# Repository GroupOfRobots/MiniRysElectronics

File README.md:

# RyśBoard Hardware Controller

This project involves the design and development of the RyśBoard hardware controller, a custom PCB created to manage a robotic system. The project aims to enhance the performance of the previous controller and involves various stages such as component selection, PCB manufacturing, and assembly. The documentation outlines the key sections of the controller, its power sources, communication interfaces, and overall production process.

## Table of Contents

1. [Key Sections of the Controller](#key-sections-of-the-controller)
   - [24V Power Supply](#24v-power-supply)
   - [5V Power Supply](#5v-power-supply)
   - [Motor Drivers](#motor-drivers)
   - [Battery Voltage Monitoring](#battery-voltage-monitoring)
   - [Battery Connectors](#battery-connectors)
   - [I/O Connectors](#io-connectors)
   - [Configurable Indicators](#configurable-indicators)
   - [Mounting Options](#mounting-options)
3. [Production Process](#production-process)
   - [Initial Project Design](#initial-project-design)
   - [Final Design in KiCad](#final-design-in-kicad)
   - [PCB Assembly](#pcb-assembly)

---

## Project Overview

This report summarizes the development of the RyśBoard hardware controller, which underwent several updates to improve its functionality. The work involved ordering components, manufacturing and assembling the PCBs, and evaluating the performance of the power supply systems.

---

## Key Sections of the Controller

### 24V Power Supply

The 24V power supply is based on the LM51231-Q1 chip and provides up to 2.5A, delivering max 60W of power. This ensures sufficient power for the stepper motors and their drivers, with a margin to accommodate future increases in power requirements.

### 5V Power Supply

A TPS565242-based 5V power supply provides up to 4A, delivering max 20W of power. It is designed to power the Raspberry Pi 4 and Raspberry Pi 5, allowing for smooth operation even with additional accessories such as fans.

### Motor Drivers

The motor drivers use L6470H chips, which meet the requirements of the stepper motors (drawing up to 1A per driver under full load). These drivers are essential for stabilizing motor control.

### Battery Voltage Monitoring

The MAX11613 ADC monitors the voltage of three batteries, each connected to a separate channel. This information is communicated to the control unit via an I²C bus, allowing real-time monitoring of battery status.

### Battery Connectors

Three battery connectors are currently used, but due to their large size, there may be a future revision to consolidate them into a single, more compact connector to optimize space on the PCB.

### I/O Connectors

The board includes dedicated connectors for each stepper motor, eight connectors for I²C sensors, and one connector each for SPI and UART devices. A 5V fan connector is also available for cooling.

### Configurable Indicators

The board is equipped with configurable LEDs (red and green) connected to GPIO pins 23 and 24 on the control unit. These can be used to signal different status conditions.

### Mounting Options

The controller is compatible with the Raspberry Pi HAT standard, allowing easy integration with Raspberry Pi systems. Care has been taken to ensure electrical insulation and secure mounting.

---

## Production Process

### Initial Project Design

The initial design phase involved five key tasks:
1. Designing the HAT-compliant add-on board for Raspberry Pi.
2. Proper placement of components for the 24V and 5V power supplies.
3. Ensuring effective heat dissipation for the motor drivers.
4. Positioning passive components for ADC and other peripherals.
5. Routing power and signal paths.

### Final Design in KiCad

The KiCad design process was iterative, focusing on:
- Component placement to ensure efficient routing.
- Optimizing power trace lengths and widths for lower heat generation and energy loss.
- Optimizing signal trace lengths and placement for lower crosstalk.
- Revising the transistor selection for the 24V power supply to improve efficiency and component availability.

Final modifications included changing the location of key components for better thermal management and adding identification markings for easier assembly.

### PCB Assembly

The assembly phase involved:
1. Ordering components primarily from Mouser Electronics.
2. Soldering the components onto the PCB.
3. Inspecting the board for any mechanical defects, such as excess solder or improper connections.

The PCB assembly required soldering both the top and bottom components, with careful attention to ensure proper connections and functionality.

---

## Project Status

- **Current version**: Final (PCB ver. 1.1)
- **Changes since last iteration**: Fixed problems with stability of internal voltage regulators of L6470H drivers

---

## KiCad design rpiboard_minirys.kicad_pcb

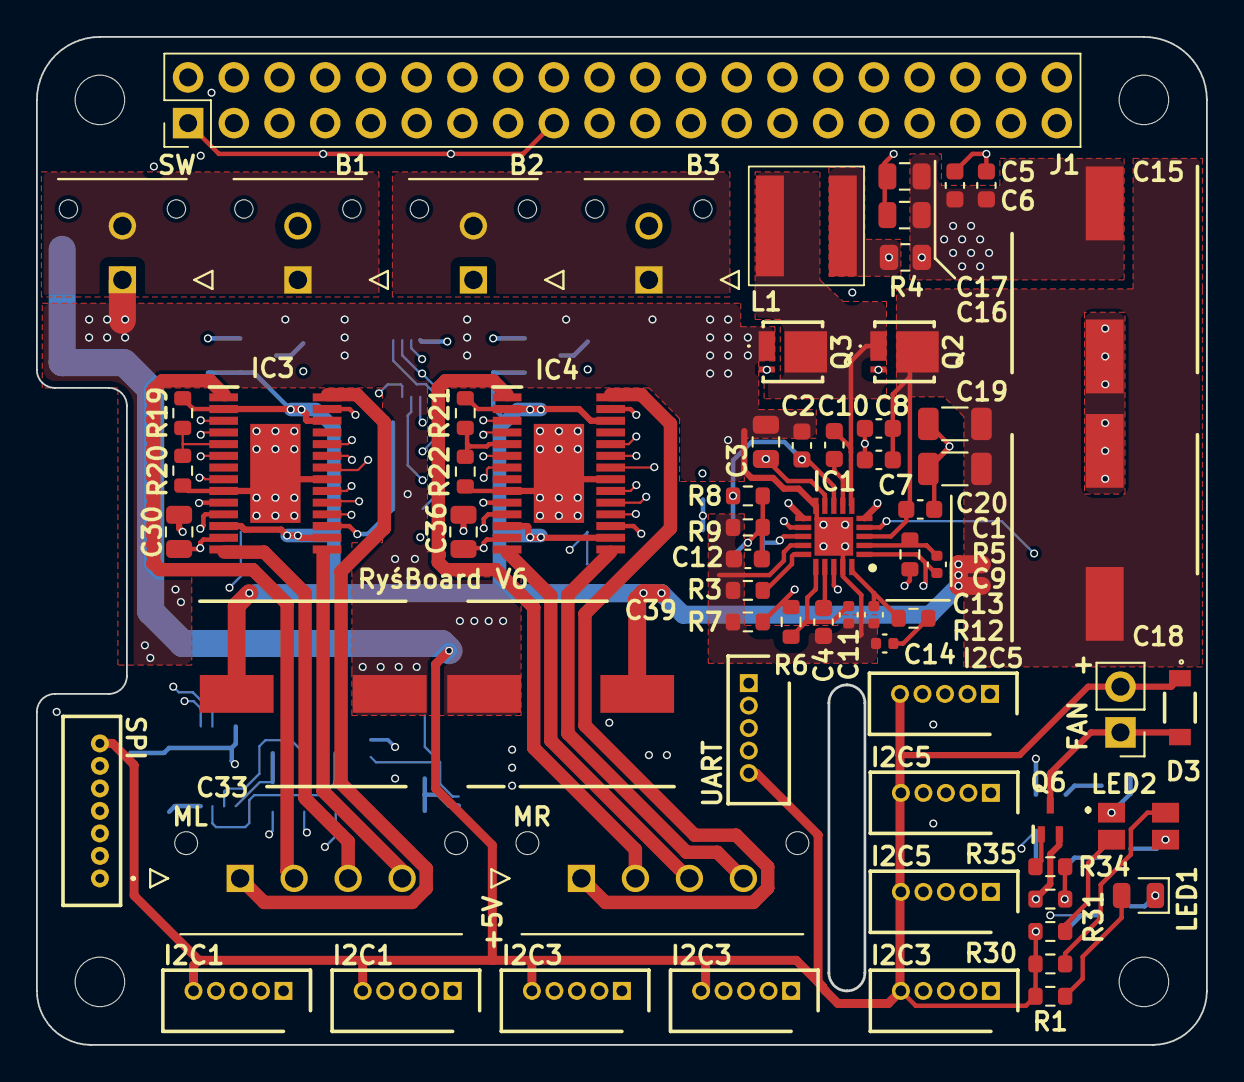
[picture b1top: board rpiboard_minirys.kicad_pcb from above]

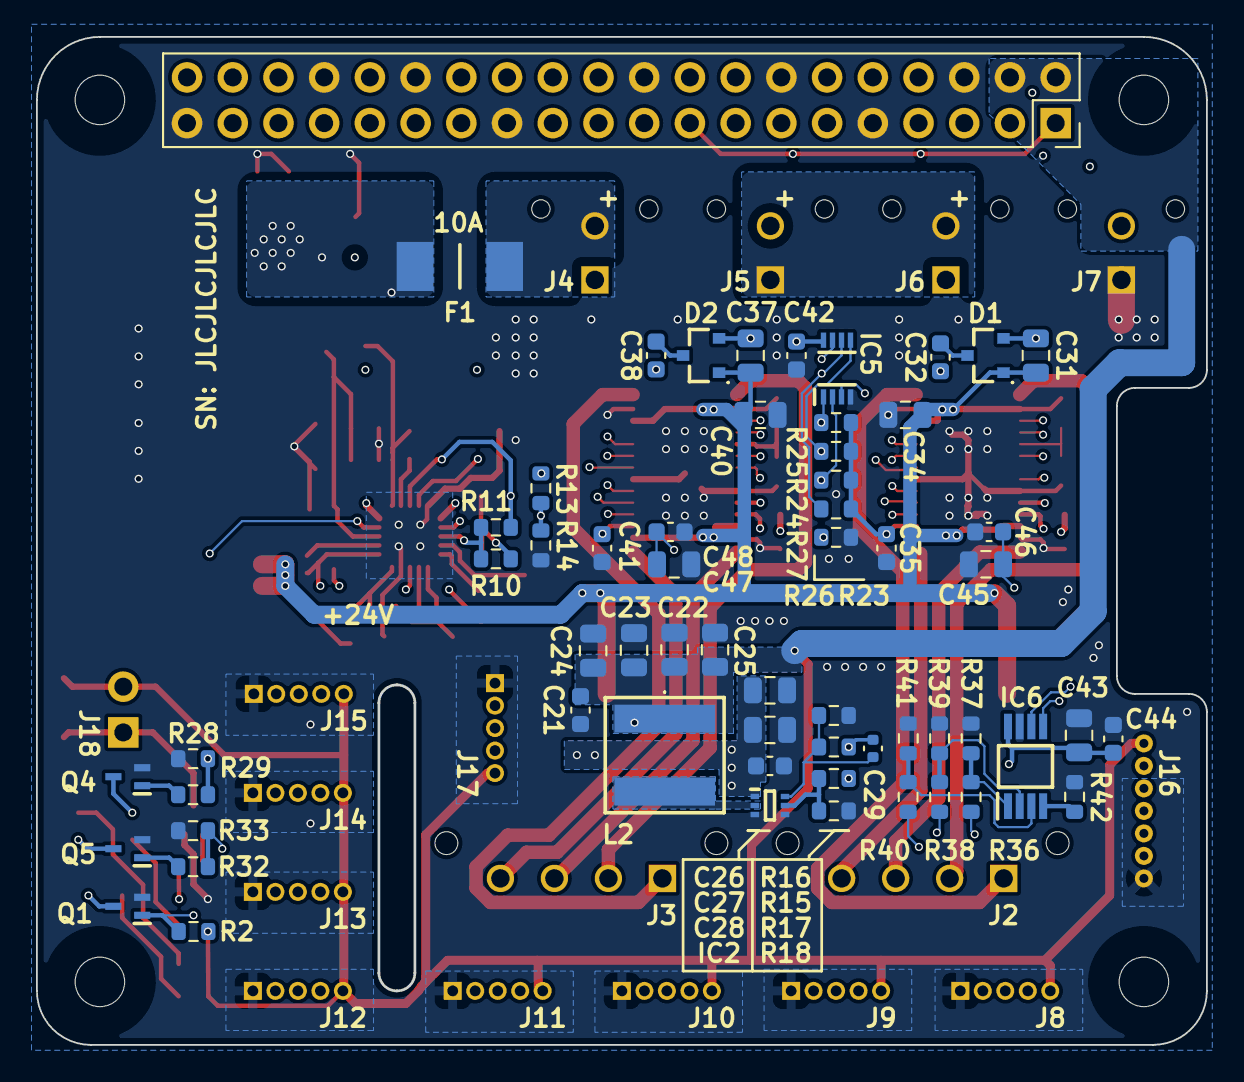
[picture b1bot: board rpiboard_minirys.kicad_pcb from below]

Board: 4 copper layers, 65.0 x 56.0 mm, 132 parts (60 on the bottom side), 93 nets.

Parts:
C1, C2, C5, C6, C7, C8, C10, C21, C28, C35, C41, C42, C44, C46, C48: 100nF; C_0603_1608Metric
C3, C43: 4.7uF; C_0805_2012Metric
C4, C12: 330nF; C_0603_1608Metric
C9: 100pF; C_0402_1005Metric
C11: 470pF; C_0402_1005Metric
C13: 22pF; C_0402_1005Metric
C14: 1.5nF; C_0402_1005Metric
C15, C18, C33, C39: 100uF; CAPAE1030X1100N
C16, C17, C22, C23, C24, C25, C26, C27, C30, C36, C45, C47: 10uF; C_0805_2012Metric
C19, C20: 10uF/50V; C_1206_3216Metric
C29: 33pF; C_0402_1005Metric
C31, C34, C37, C40: 220nF; C_0805_2012Metric
C32, C38: 10nF; C_0603_1608Metric
D1, D2: BAV99; BAV99215
D3: BAT54GWX; SOD123
F1: 10A Fuse; FUSC6126X270N
H1, H2, H3, H4: MountingHole; RPi_Hat_Mounting_Hole
IC1: LM51231QRGRRQ1; QFN50P350X350X100-21N-D
IC2: TPS564242DRLR; SOTFL50P160X60-6N
IC3, IC4: L6470H; SOP65P640X120-29N
IC5: 74AUP2G00DC,125; SOP50P310X100-8N
IC6: MAX11613EUA+T; SOP65P490X110-8N
J1: RPi_GPIO; PinSocket_2x20_P2.54mm_Vertical
J2: Motor_L; 43650-04YY_151617
J3: Motor_R; 43650-04YY_151617
J4: B_Cell_3; 43045-02YY_121314
J5: B_Cell_2; 43045-02YY_121314
J6: B_Cell_1; 43045-02YY_121314
J7: SW; 43045-02YY_121314
J8: Temp_Sensor; 530470510
J9: IMU_Sensor; 530470510
J10: ToF1_Sensor; 530470510
J11: ToF2_Sensor; 530470510
J12: ToF3_Sensor; 530470510
J13: ToF4_Sensor; 530470510
J14: ToF5_Sensor; 530470510
J15: ToF6_Sensor; 530470510
J16: SPI_Connector; 530470710
J17: UART_Connector; 530470510
J18: Fan_Connector; PinHeader_1x02_P2.54mm_Vertical
L1: SRP6060FA-4R7M; SRP6060FA4R7M
L2: SRP6050CA-1R8M; SRP6050CA1R8M
LED1: GREEN; LED_0805_2012Metric
LED2: LSG_T676-P7Q7-1+N7P7-24; LSGT676P7Q71N7P724
Q1, Q4, Q5, Q6: DMG1012T-7; SOT50P160X80-3N
Q2, Q3: ISZ065N03L5S; ISZ065N03L5SATMA1
R1, R29, R30, R31, R32, R35: 150R; R_0603_1608Metric
R2, R9: 12k; R_0603_1608Metric
R3: 32.4k/.1%; R_0603_1608Metric
R4: 0.006R; R_0805_2012Metric
R5: 100R; R_0603_1608Metric
R6: 21k; R_0603_1608Metric
R7: 14k; R_0603_1608Metric
R8: 80.6k; R_0603_1608Metric
R10, R11, R13, R14: 0R; R_0603_1608Metric
R12: 59k; R_0603_1608Metric
R15: 220k; R_0603_1608Metric
R16: 30k; R_0603_1608Metric
R17, R28, R33, R34: 100k; R_0603_1608Metric
R18: 17.4k; R_0603_1608Metric
R19, R21: 27k; R_0603_1608Metric
R20, R22, R37, R39, R41, R42: 10k; R_0603_1608Metric
R23, R24, R25, R26, R27: 38.3k; R_0603_1608Metric
R36: 15k; R_0603_1608Metric
R38: 36k; R_0603_1608Metric
R40: 56k; R_0603_1608Metric

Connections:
+3.3V: C30.1, C35.2, C36.1, C41.2, C42.1, C43.1, C44.1, IC3.4 (SW), IC3.17 (VDD), IC4.4 (SW), IC4.17 (VDD), IC5.8 (VCC), IC6.8 (VDD), J1.1, J1.17, R24.1, R25.1, R26.1, R27.1
+5V: C21.1, C22.1, C23.1, C24.1, C25.1, C29.2, D3.1 (K), J1.2, J1.4, J8.5, J9.5, J10.5, J11.5, J12.5, J13.5, J14.5, J15.5, J16.7, J17.5, J18.2, L2.1, R1.1, R2.2, R15.1, R30.2, R31.2
+24V: C1.2, C7.1, C8.1, C18.1, C19.1, C20.1, C31.2, C33.1, C34.2, C37.2, C39.1, C40.2, D1.1 (A), D2.1 (A), IC1.3 (VOUT/SENSE), IC3.2 (VSA_1), IC3.12 (VSB_1), IC3.16 (VSB_2), IC3.26 (VSA_2), IC4.2 (VSA_1), IC4.12 (VSB_1), IC4.16 (VSB_2), IC4.26 (VSA_2), Q2.3 (D), R19.2, R21.2
/Connectors/CELL_1: J5.1, J6.2, R36.1
/Connectors/CELL_2: J4.1, J5.2, R38.1
/Connectors/CELL_3: F1.2, J4.2, R40.1
/Connectors/FAN_PWM: J1.12, R34.1, R35.1
/Connectors/FAN_SW: D3.2 (A), J18.1, Q6.3 (D)
/Connectors/I2C1_SCL: IC6.5 (SCL), J1.5, J8.3, J9.3
/Connectors/I2C1_SDA: IC6.6 (SDA), J1.3, J8.4, J9.4
/Connectors/I2C3_SCL: J1.29, J10.3, J11.3, J12.3
/Connectors/I2C3_SDA: J1.7, J10.4, J11.4, J12.4
/Connectors/I2C5_SCL: J1.33, J13.3, J14.3, J15.3
/Connectors/I2C5_SDA: J1.32, J13.4, J14.4, J15.4
/Connectors/LED_GREEN: J1.18, R32.2, R33.1
/Connectors/LED_RED: J1.16, R28.2, R29.1
/Connectors/ML_OUT1A: IC3.1 (OUT1A), J2.2
/Connectors/ML_OUT1B: IC3.14 (OUT1B), J2.3
/Connectors/ML_OUT2A: IC3.28 (OUT2A), J2.1
/Connectors/ML_OUT2B: IC3.15 (OUT2B), J2.4
/Connectors/MR_OUT1A: IC4.1 (OUT1A), J3.2
/Connectors/MR_OUT1B: IC4.14 (OUT1B), J3.3
/Connectors/MR_OUT2A: IC4.28 (OUT2A), J3.1
/Connectors/MR_OUT2B: IC4.15 (OUT2B), J3.4
/Connectors/M_BUSY: IC5.3 (2Y), J1.13
/Connectors/M_FLAG: IC5.7 (1Y), J1.11
/Connectors/SPI_CLK: IC3.19 (CK), IC4.19 (CK), J1.23, J16.4
/Connectors/SPI_IRQ: J1.22, J16.2
/Connectors/SPI_MISO: IC4.18 (SDO), J1.21, J16.5
/Connectors/SPI_MOSI: IC3.20 (SDI), J1.19, J16.6
/Connectors/TOF1_EN: J1.31, J10.2
/Connectors/TOF2_EN: J1.36, J11.2
/Connectors/TOF3_EN: J1.35, J12.2
/Connectors/TOF4_EN: J1.38, J13.2
/Connectors/TOF5_EN: J1.40, J14.2
/Connectors/TOF6_EN: J1.37, J15.2
/Connectors/UART_RX: J1.10, J17.4
/Connectors/UART_TX: J1.8, J17.3
/Connectors/~M_STBY: IC3.3 (~STBY/RST), IC4.3 (~STBY/RST), J1.15, R23.2
/Connectors/~SPI_CS_E: J1.26, J16.3
/Connectors/~SPI_CS_M: IC3.23 (~CS), IC4.23 (~CS), J1.24
/Motor_Controllers/3V_VREG_ML: C45.1, C46.1, IC3.6 (VREG)
/Motor_Controllers/3V_VREG_MR: C47.1, C48.1, IC4.6 (VREG)
/Motor_Controllers/CLK_SYNC: IC3.8 (OSCOUT), IC4.7 (OSCIN)
/Motor_Controllers/ML_ADCIN: IC3.5 (ADCIN), R19.1, R20.2
/Motor_Controllers/ML_CP: C32.2, IC3.10 (CP)
/Motor_Controllers/ML_VBOOT: C31.1, D1.2 (K), IC3.11 (VBOOT)
/Motor_Controllers/MR_ADCIN: IC4.5 (ADCIN), R21.1, R22.2
/Motor_Controllers/MR_CP: C38.2, IC4.10 (CP)
/Motor_Controllers/MR_VBOOT: C37.1, D2.2 (K), IC4.11 (VBOOT)
/Motor_Controllers/SPI_BRIDGE: IC3.18 (SDO), IC4.20 (SDI)
/Motor_Controllers/~ML_BUSY: IC3.22 (~BUSY/SYNC), IC5.5 (2A), R24.2
/Motor_Controllers/~ML_FLAG: IC3.24 (~FLAG), IC5.1 (1A), R25.2
/Motor_Controllers/~MR_BUSY: IC4.22 (~BUSY/SYNC), IC5.6 (2B), R26.2
/Motor_Controllers/~MR_FLAG: IC4.24 (~FLAG), IC5.2 (1B), R27.2
/Supply_24V/COMP: C13.1, IC1.20 (COMP), R12.1
/Supply_24V/CSN: C9.1, IC1.2 (CSN), R5.1
/Supply_24V/HB: C10.1, IC1.7 (HB)
/Supply_24V/HO: IC1.5 (HO), Q2.2 (G)
/Supply_24V/LO: IC1.11 (LO), Q3.2 (G)
/Supply_24V/MODE: IC1.12 (MODE), R13.1, R14.1
/Supply_24V/SW: C10.2, IC1.6 (SW), L1.2, Q2.1 (S), Q3.3 (D)
/Supply_24V/TRK: IC1.18 (TRK), R6.2, R7.1
/Supply_24V/UVLO: IC1.13 (UVLO/EN), R10.1, R11.1
/Supply_24V/VCC_REG: C3.1, IC1.9 (VCC), R13.2
/Supply_24V/VREF: C11.1, IC1.16 (VREF/_RANGE), R6.1
GND: C1.1, C2.2, C3.2, C4.1, C5.2, C6.2, C7.2, C8.2, C11.2, C12.2, C13.2, C14.2, C15.2, C16.2, C17.2, C18.2, C19.2, C20.2, C21.2, C22.2, C23.2, C24.2, C25.2, C26.2, C27.2, C28.2, C30.2, C33.2, C34.1, C35.1, C36.2, C39.2, C40.1, C41.1, C42.2, C43.2, C44.2, C45.2, C46.2, C47.2, C48.2, IC1.10 (PGND), IC1.14 (SYNC/DITHER/VH), IC1.19 (AGND), IC1.21 (EP), IC2.3 (GND), IC2.4 (AGND), IC3.9 (AGND), IC3.13 (PGND_1), IC3.21 (DGND), IC3.27 (PGND_2), IC3.29 (EP), IC4.9 (AGND), IC4.13 (PGND_1), IC4.21 (DGND), IC4.27 (PGND_2), IC4.29 (EP), IC5.4 (GND), IC6.7 (GND), J1.6, J1.9, J1.14, J1.20, J1.25, J1.30, J1.34, J1.39, J7.1, J8.1, J9.1, J10.1, J11.1, J12.1, J13.1, J14.1, J15.1, J16.1, J17.1, Q1.2 (S), Q3.1 (S), Q4.2 (S), Q5.2 (S), Q6.2 (S), R3.2, R7.2, R9.2, R14.2, R16.2, R18.2, R20.1, R22.1, R23.1, R28.1, R33.2, R34.2, R37.2, R39.2, R41.2, R42.2
unnamed: C12.1, R8.2, R9.1, R10.2
unnamed: C14.1, R12.2
unnamed: C32.1, D1.3 (common)
unnamed: C38.1, D2.3 (common)
unnamed: IC1.4 (PGOOD), Q1.1 (G), R2.1
unnamed: IC1.15 (RT), R3.1
unnamed: C4.2, IC1.17 (SS)
unnamed: IC2.5 (EN), R17.2, R18.1
unnamed: C29.1, IC2.6 (FB), R15.2, R16.1
unnamed: IC2.2 (SW), L2.2
unnamed: IC6.1 (AIN0), R36.2, R37.1
unnamed: IC6.2 (AIN1), R38.2, R39.1
unnamed: IC6.3 (AIN2), R40.2, R41.1
unnamed: IC6.4 (AIN3/REF), R42.1
unnamed: J6.1, J7.2
unnamed: L1.1, R4.2, R5.2
unnamed: LED1.2 (A), R1.2
unnamed: LED1.1 (K), Q1.3 (D)
unnamed: LED2.1 (A1), Q4.3 (D)
unnamed: LED2.3 (A2), Q5.3 (D)
unnamed: LED2.2 (K1), R30.1
unnamed: LED2.4 (K2), R31.1
unnamed: Q4.1 (G), R29.2
unnamed: Q5.1 (G), R32.1
unnamed: Q6.1 (G), R35.2
VCC: C2.1, C5.1, C6.1, C9.2, C15.1, C16.1, C17.1, C26.1, C27.1, C28.1, F1.1, IC1.1 (CSP), IC1.8 (BIAS), IC2.1 (VIN), R4.1, R8.1, R11.2, R17.1

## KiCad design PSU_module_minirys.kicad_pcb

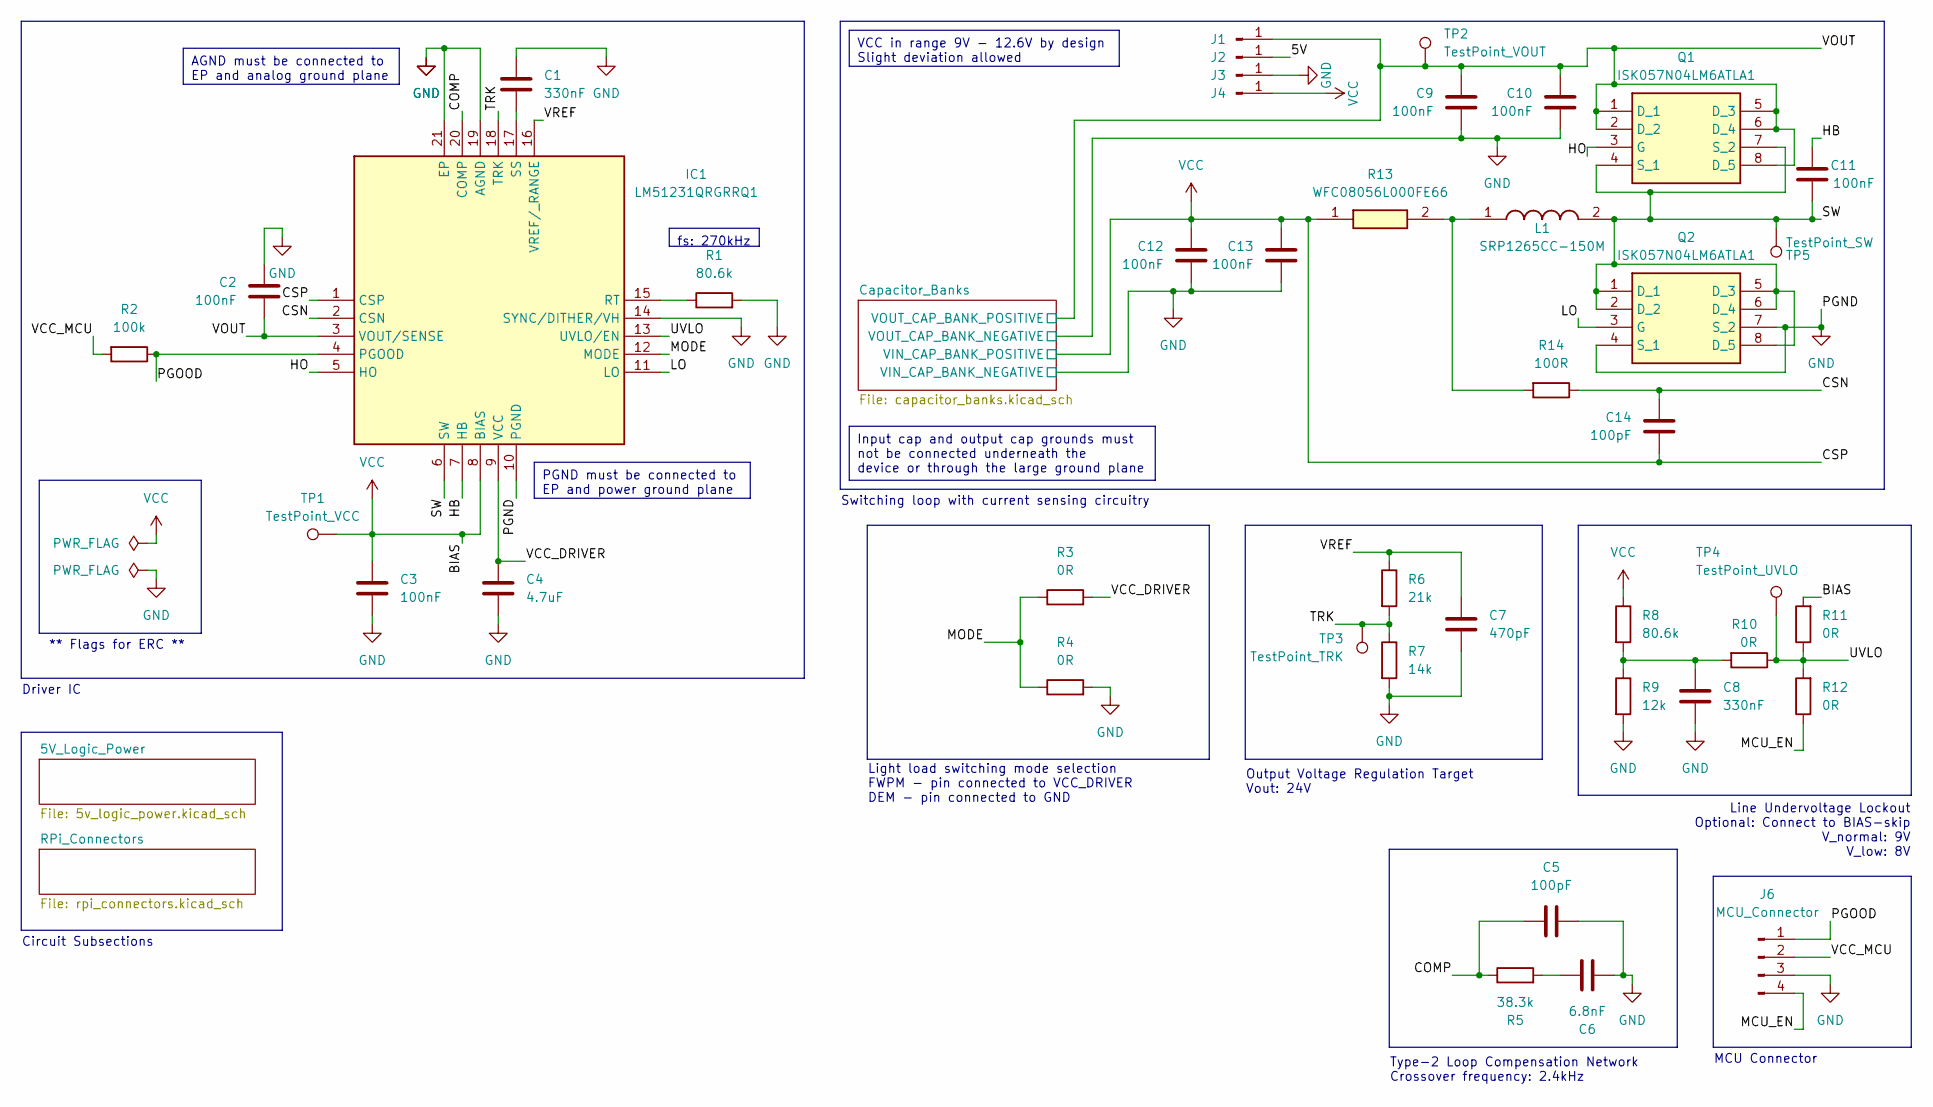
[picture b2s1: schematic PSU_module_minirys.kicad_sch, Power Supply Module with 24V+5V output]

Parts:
C1, C8: 330nF; C_0603_1608Metric
C2, C3, C9, C10, C11, C12, C13: 100nF; C_0603_1608Metric
C4: 4.7uF; C_0805_2012Metric
C5, C14: 100pF; C_0603_1608Metric
C6: 6.8nF; C_0603_1608Metric
C7: 470pF; C_0603_1608Metric
IC1: LM51231QRGRRQ1; QFN50P350X350X100-21N-D; Mouser Part Number 595-LM51231QRGRRQ1
J1, J2, J3, J4: Conn_01x01_Pin; TestPoint_Pad_2.0x2.0mm
J6: MCU_Connector; PinSocket_1x04_P2.54mm_Vertical
L1: SRP1265CC-150M; INDPM135125X650N; Manufacturer_Part_Number SRP1265CC-150M
Q1, Q2: ISK057N04LM6ATLA1; Manufacturer_Part_Number ISK057N04LM6ATLA1
R1, R8: 80.6k; R_0603_1608Metric
R2: 100k; R_0603_1608Metric
R3, R4, R10, R11, R12: 0R; R_0603_1608Metric
R5: 38.3k; R_0603_1608Metric
R6: 21k; R_0603_1608Metric
R7: 14k; R_0603_1608Metric
R9: 12k; R_0603_1608Metric
R13: WFC08056L000FE66; RESC2013X85N; Mouser Part Number 71-WFC08056L000FE66
R14: 100R; R_0603_1608Metric
TP1: TestPoint_VCC; TestPoint_Pad_D1.0mm
TP2: TestPoint_VOUT; TestPoint_Pad_D1.0mm
TP3: TestPoint_TRK; TestPoint_Pad_D1.0mm
TP4: TestPoint_UVLO; TestPoint_Pad_D1.0mm
TP5: TestPoint_SW; TestPoint_Pad_D1.0mm

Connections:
/5V: J2.1
/COMP: C5.1, IC1.20 (COMP), R5.1
/CSN: C14.1, IC1.2 (CSN), R14.1
/HB: C11.1, IC1.7 (HB)
/HO: IC1.5 (HO), Q1.3 (G)
/LO: IC1.11 (LO), Q2.3 (G)
/MCU_EN: J6.4, R12.1
/MODE: IC1.12 (MODE), R3.1, R4.1
/PGOOD: IC1.4 (PGOOD), J6.1, R2.1
/SW: C11.2, IC1.6 (SW), L1.2, Q1.4 (S_1), Q1.7 (S_2), Q2.1 (D_1), Q2.2 (D_2), Q2.5 (D_3), Q2.6 (D_4), Q2.8 (D_5), TP5.1
/TRK: IC1.18 (TRK), R6.2, R7.1, TP3.1
/UVLO: IC1.13 (UVLO/EN), R10.1, R11.1, R12.2, TP4.1
/VCC_DRIVER: C4.1, IC1.9 (VCC), R3.2
/VCC_MCU: J6.2, R2.2
/VOUT: C2.2, C9.1, C10.1, IC1.3 (VOUT/SENSE), J1.1, Q1.1 (D_1), Q1.2 (D_2), Q1.5 (D_3), Q1.6 (D_4), Q1.8 (D_5), TP2.1; also elsewhere on the board
/VREF: C7.1, IC1.16 (VREF/_RANGE), R6.1
GND: C1.1, C2.1, C3.2, C4.2, C5.2, C6.2, C7.2, C8.2, C9.2, C10.2, C12.2, C13.2, IC1.10 (PGND), IC1.14 (SYNC/DITHER/VH), IC1.19 (AGND), IC1.21 (EP), J3.1, J6.3, Q2.4 (S_1), Q2.7 (S_2), R1.2, R4.2, R7.2, R9.2; also elsewhere on the board
unnamed: C6.1, R5.2
unnamed: C8.1, R8.2, R9.1, R10.2
unnamed: IC1.15 (RT), R1.1
unnamed: C1.2, IC1.17 (SS)
unnamed: L1.1, R13.2, R14.2
VCC: C3.1, C12.1, C13.1, C14.2, IC1.1 (CSP), IC1.8 (BIAS), J4.1, R8.1, R11.2, R13.1, TP1.1; also elsewhere on the board

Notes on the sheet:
PGND must be connected to EP and power ground plane
Input cap and output cap grounds must not be connected underneath the device or through the large ground plane
AGND must be connected to EP and analog ground plane
fs: 270kHz
VCC in range 9V - 12.6V by design Slight deviation allowed
** Flags for ERC **
MCU Connector
Circuit Subsections
Line Undervoltage Lockout Optional: Connect to BIAS-skip V_normal: 9V V_low: 8V
Driver IC
Output Voltage Regulation Target Vout: 24V
Light load switching mode selection FWPM - pin connected to VCC_DRIVER DEM - pin connected to GND
Type-2 Loop Compensation Network Crossover frequency: 2.4kHz
Switching loop with current sensing circuitry

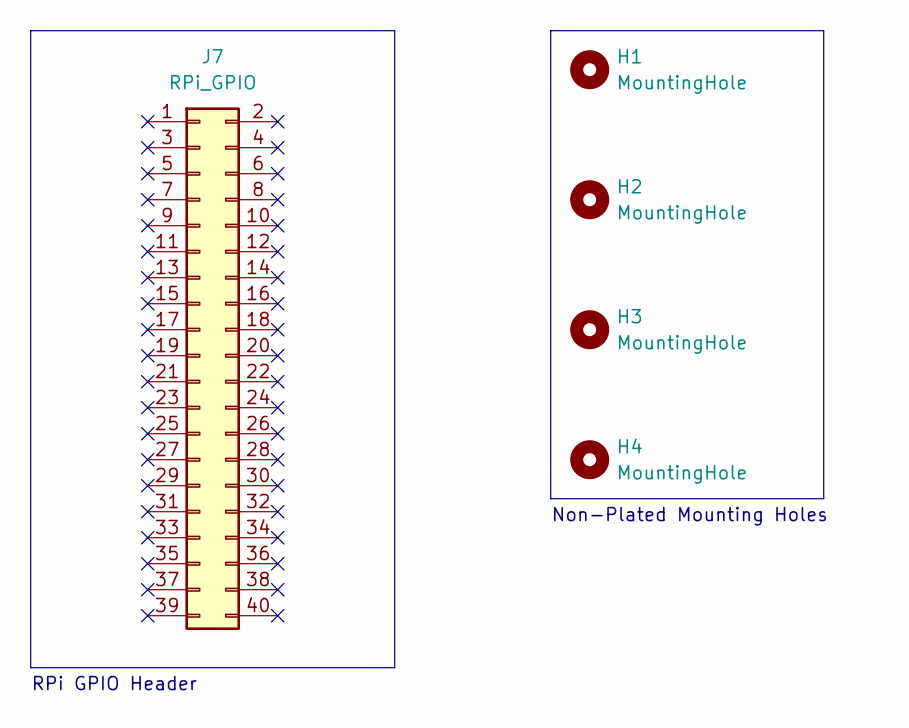
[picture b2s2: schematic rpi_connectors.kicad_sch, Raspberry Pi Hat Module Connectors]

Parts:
H1, H2, H3, H4: MountingHole; RPi_Hat_Mounting_Hole
J7: RPi_GPIO; PinSocket_2x20_P2.54mm_Vertical

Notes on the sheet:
Non-Plated Mounting Holes
RPi GPIO Header

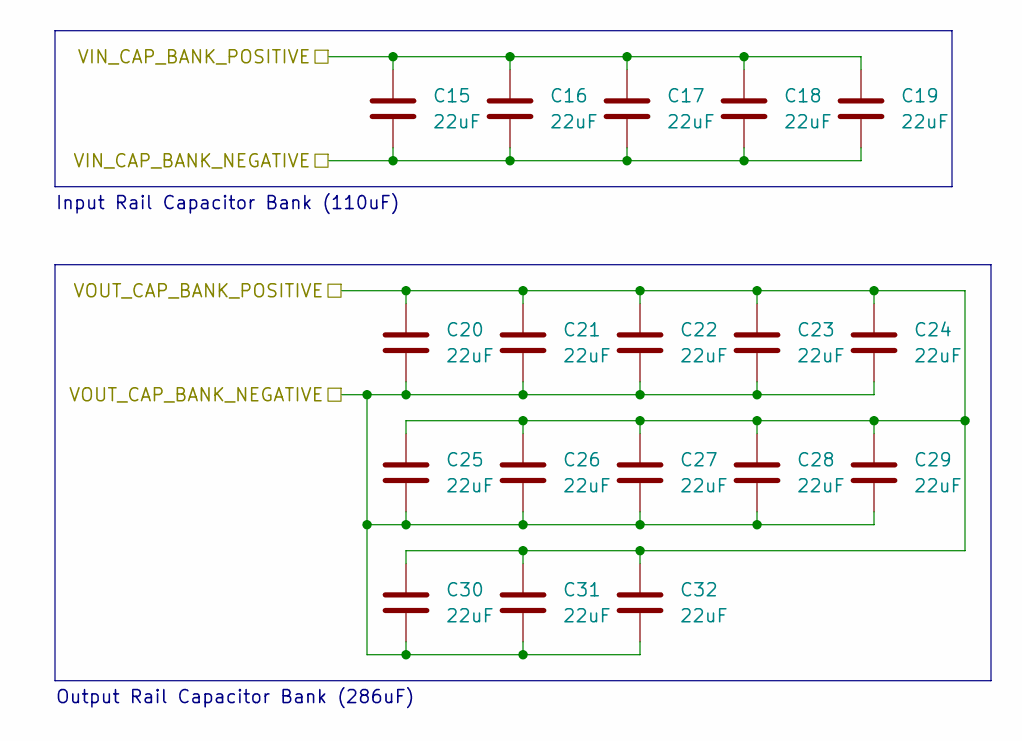
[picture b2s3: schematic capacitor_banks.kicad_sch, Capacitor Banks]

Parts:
C15, C16, C17, C18, C19, C20, C21, C22, C23, C24, C25, C26, C27, C28, C29, C30, C31, C32: 22uF; C_0805_2012Metric

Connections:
/VOUT: C20.1, C21.1, C22.1, C23.1, C24.1, C25.1, C26.1, C27.1, C28.1, C29.1, C30.1, C31.1, C32.1; also elsewhere on the board
GND: C15.2, C16.2, C17.2, C18.2, C19.2, C20.2, C21.2, C22.2, C23.2, C24.2, C25.2, C26.2, C27.2, C28.2, C29.2, C30.2, C31.2, C32.2; also elsewhere on the board
VCC: C15.1, C16.1, C17.1, C18.1, C19.1; also elsewhere on the board

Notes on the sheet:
Output Rail Capacitor Bank (286uF)
Input Rail Capacitor Bank (110uF)

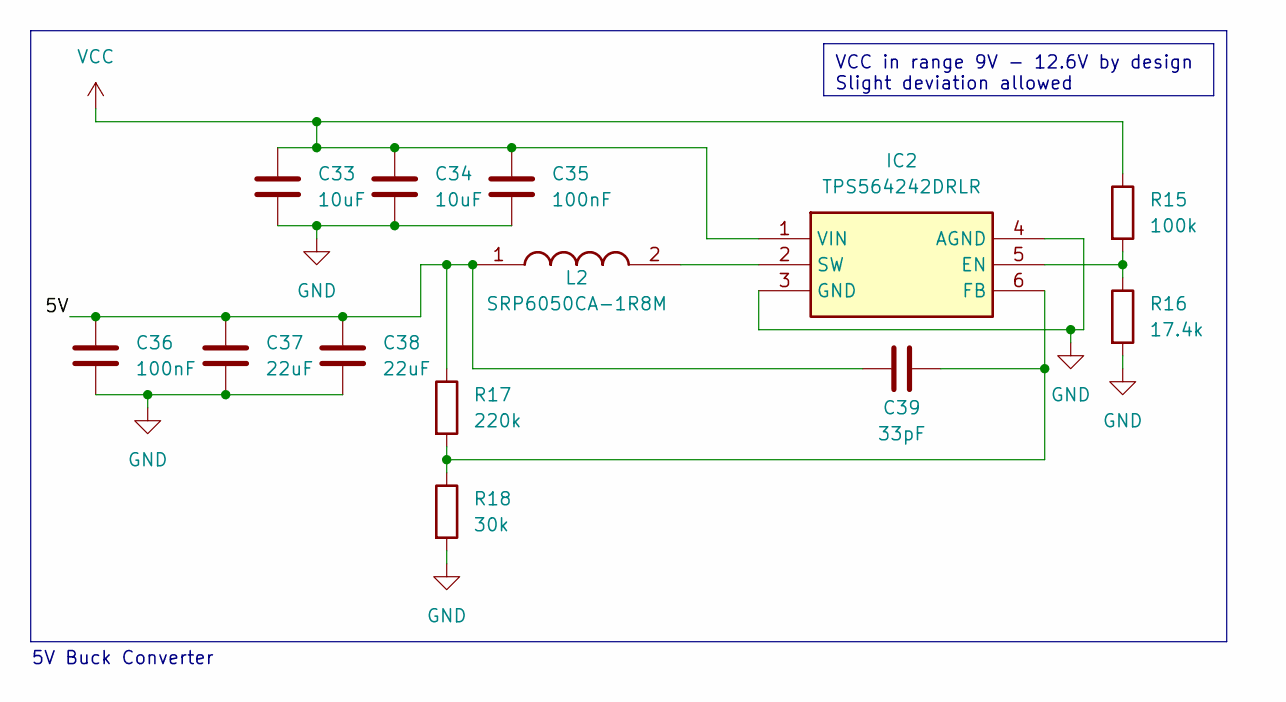
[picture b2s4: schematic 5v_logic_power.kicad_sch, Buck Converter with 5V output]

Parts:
C33, C34: 10uF; C_0805_2012Metric
C35, C36: 100nF; C_0603_1608Metric
C37, C38: 22uF; C_0805_2012Metric
C39: 33pF; C_0402_1005Metric
IC2: TPS564242DRLR; SOTFL50P160X60-6N; Mouser Part Number 595-TPS564242DRLR
L2: SRP6050CA-1R8M; SRP6050CA1R8M; Mouser Part Number 652-SRP6050CA-1R8M
R15: 100k; R_0603_1608Metric
R16: 17.4k; R_0603_1608Metric
R17: 220k; R_0603_1608Metric
R18: 30k; R_0603_1608Metric

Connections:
/5V_Logic_Power/5V: C36.1, C37.1, C38.1, C39.2, L2.1, R17.1
GND: C33.2, C34.2, C35.2, C36.2, C37.2, C38.2, IC2.3 (GND), IC2.4 (AGND), R16.2, R18.2; also elsewhere on the board
unnamed: IC2.5 (EN), R15.2, R16.1
unnamed: C39.1, IC2.6 (FB), R17.2, R18.1
unnamed: IC2.2 (SW), L2.2
VCC: C33.1, C34.1, C35.1, IC2.1 (VIN), R15.1; also elsewhere on the board

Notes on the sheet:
VCC in range 9V - 12.6V by design Slight deviation allowed
5V Buck Converter

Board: 4 copper layers, 78 parts (8 on the bottom side), 26 nets, no tracks yet.

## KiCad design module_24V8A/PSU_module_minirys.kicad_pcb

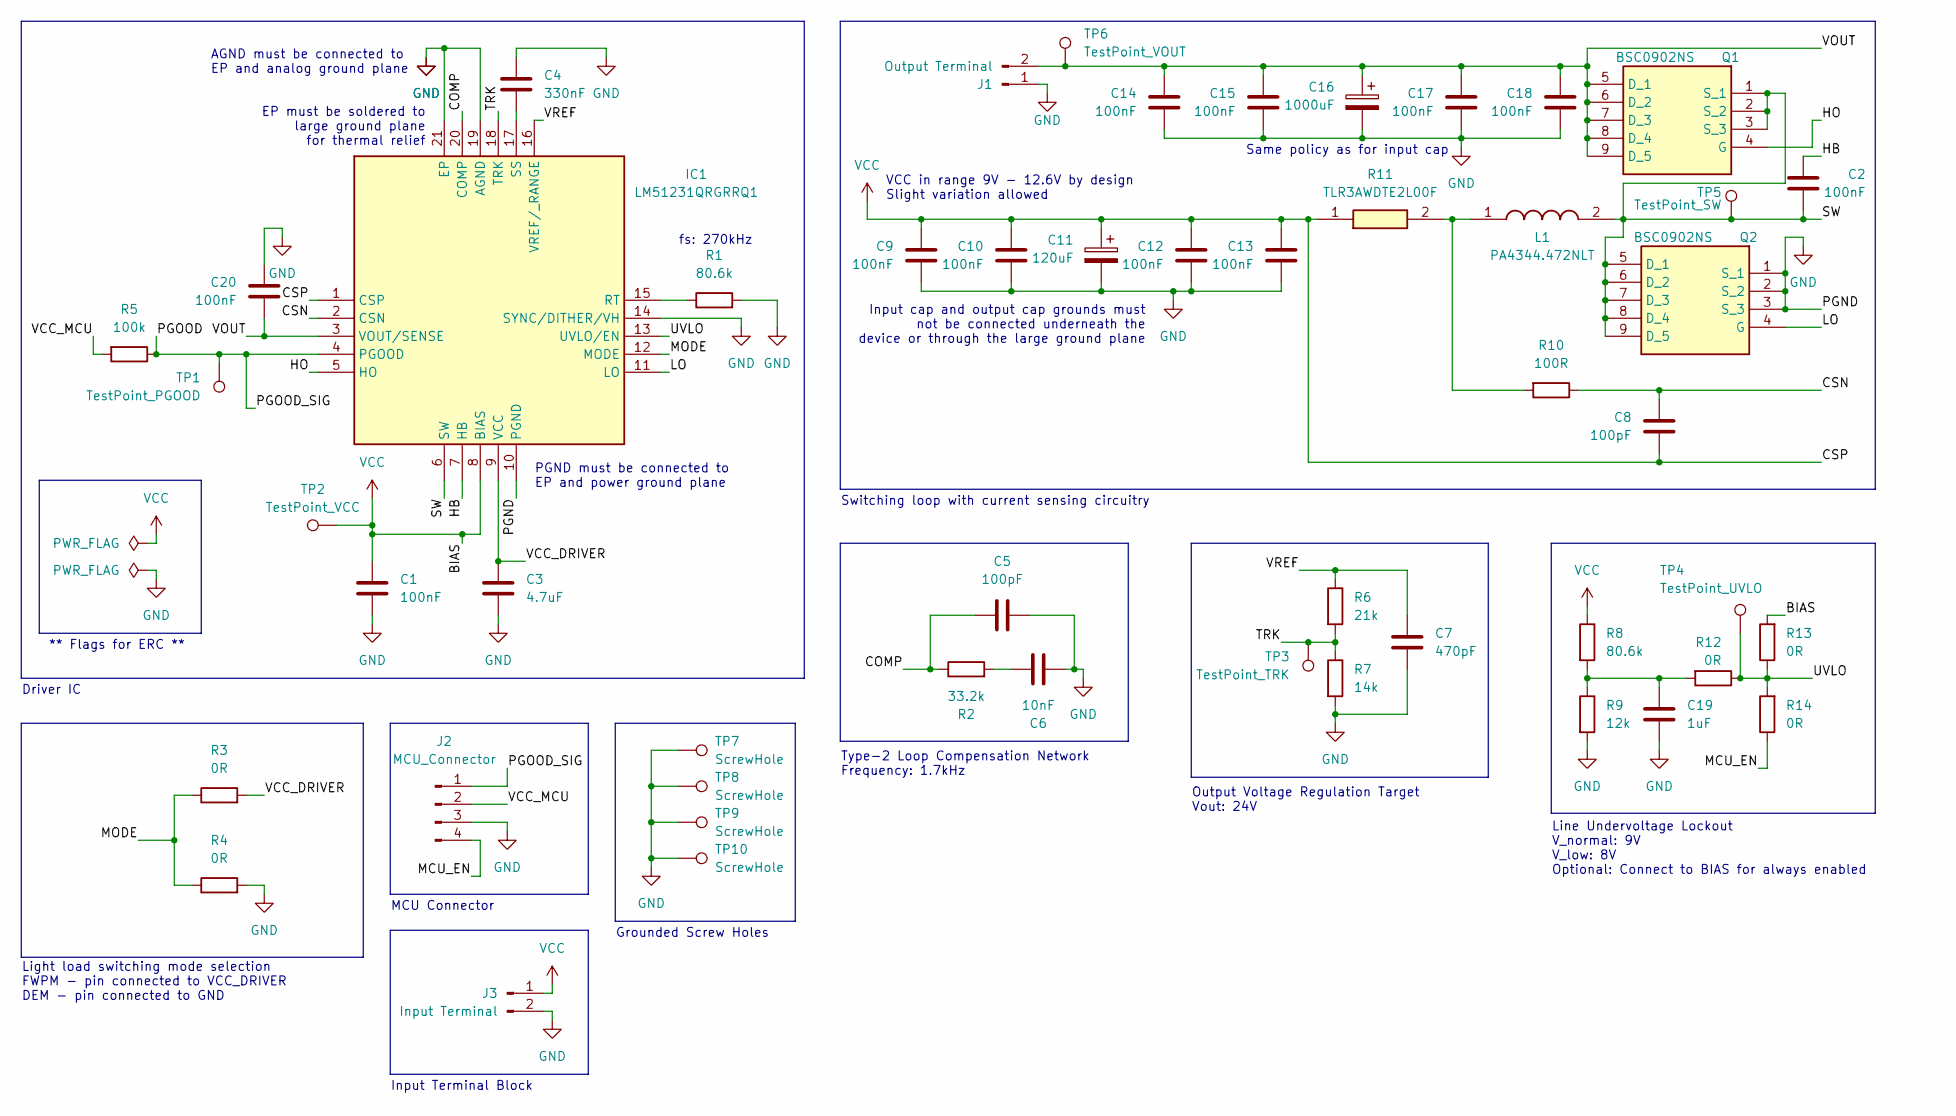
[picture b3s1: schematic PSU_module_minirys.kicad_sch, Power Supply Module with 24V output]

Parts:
C1, C2, C9, C10, C12, C13, C14, C15, C17, C18: 100nF; C_0805_2012Metric
C3: 4.7uF; C_1206_3216Metric
C4: 330nF; C_0805_2012Metric
C5, C8: 100pF; C_0603_1608Metric
C6: 10nF; C_0603_1608Metric
C7: 470pF; C_0603_1608Metric
C11: 120uF; CP_Radial_D10.0mm_P5.00mm
C16: 1000uF; CP_Radial_D12.5mm_P5.00mm
C19: 1uF; C_0805_2012Metric
C20: 100nF; C_0603_1608Metric
IC1: LM51231QRGRRQ1; QFN50P350X350X100-21N-D; Mouser Part Number 595-LM51231QRGRRQ1
J1: Output Terminal; Altech_AK300_1x02_P5.00mm_45-Degree
J2: MCU_Connector; PinHeader_1x04_P1.00mm_Vertical
J3: Input Terminal; Altech_AK300_1x02_P5.00mm_45-Degree
L1: PA4344.472NLT; PA4344472NLT; Mouser Part Number 673-PA4344.472NLT
Q1, Q2: BSC0902NS; PG-TDSON-8_1; Mouser Part Number 726-BSC0902NS
R1, R8: 80.6k; R_0603_1608Metric
R2: 33.2k; R_0603_1608Metric
R3, R4, R12, R13, R14: 0R; R_0805_2012Metric
R5: 100k; R_0603_1608Metric
R6: 21k; R_0603_1608Metric
R7: 14k; R_0603_1608Metric
R9: 12k; R_0603_1608Metric
R10: 100R; R_0603_1608Metric
R11: TLR3AWDTE2L00F; RESC6432X85N; Mouser Part Number 660-TLR3AWD2L00F
TP1: TestPoint_PGOOD; TestPoint_Pad_D1.0mm
TP2: TestPoint_VCC; TestPoint_Pad_D1.0mm
TP3: TestPoint_TRK; TestPoint_Pad_D1.0mm
TP4: TestPoint_UVLO; TestPoint_Pad_D1.0mm
TP5: TestPoint_SW; TestPoint_Pad_D1.0mm
TP6: TestPoint_VOUT; TestPoint_Pad_D1.0mm
TP7, TP8, TP9, TP10: ScrewHole; MountingHole_2.7mm_M2.5_Pad

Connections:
/COMP: C5.1, IC1.20 (COMP), R2.1
/CSN: C8.1, IC1.2 (CSN), R10.1
/HB: C2.1, IC1.7 (HB)
/HO: IC1.5 (HO), Q1.4 (G)
/LO: IC1.11 (LO), Q2.4 (G)
/MCU_EN: J2.4, R14.1
/MODE: IC1.12 (MODE), R3.1, R4.1
/PGOOD: IC1.4 (PGOOD), J2.1, R5.1, TP1.1
/SW: C2.2, IC1.6 (SW), L1.2, Q1.1 (S_1), Q1.2 (S_2), Q1.3 (S_3), Q2.5 (D_1), Q2.6 (D_2), Q2.7 (D_3), Q2.8 (D_4), Q2.9 (D_5), TP5.1
/TRK: IC1.18 (TRK), R6.2, R7.1, TP3.1
/UVLO: IC1.13 (UVLO/EN), R12.1, R13.1, R14.2, TP4.1
/VCC_DRIVER: C3.1, IC1.9 (VCC), R3.2
/VCC_MCU: J2.2, R5.2
/VOUT: C14.1, C15.1, C16.1, C17.1, C18.1, C20.2, IC1.3 (VOUT/SENSE), J1.2, Q1.5 (D_1), Q1.6 (D_2), Q1.7 (D_3), Q1.8 (D_4), Q1.9 (D_5), TP6.1
/VREF: C7.1, IC1.16 (VREF/_RANGE), R6.1
GND: C1.2, C3.2, C4.1, C5.2, C6.2, C7.2, C9.1, C10.1, C11.2, C12.2, C13.2, C14.2, C15.2, C16.2, C17.2, C18.2, C19.2, C20.1, IC1.10 (PGND), IC1.14 (SYNC/DITHER/VH), IC1.19 (AGND), IC1.21 (EP), J1.1, J2.3, J3.2, Q2.1 (S_1), Q2.2 (S_2), Q2.3 (S_3), R1.2, R4.2, R7.2, R9.2, TP7.1, TP8.1, TP9.1, TP10.1
unnamed: C6.1, R2.2
unnamed: C19.1, R8.2, R9.1, R12.2
unnamed: IC1.15 (RT), R1.1
unnamed: C4.2, IC1.17 (SS)
unnamed: L1.1, R10.2, R11.2
VCC: C1.1, C8.2, C9.2, C10.2, C11.1, C12.1, C13.1, IC1.1 (CSP), IC1.8 (BIAS), J3.1, R8.1, R11.1, R13.2, TP2.1

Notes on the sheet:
EP must be soldered to large ground plane for thermal relief
VCC in range 9V - 12.6V by design Slight variation allowed
** Flags for ERC **
Input cap and output cap grounds must not be connected underneath the device or through the large ground plane
PGND must be connected to EP and power ground plane
Input Terminal Block
Grounded Screw Holes
AGND must be connected to EP and analog ground plane
MCU Connector
Line Undervoltage Lockout V_normal: 9V V_low: 8V Optional: Connect to BIAS for always enabled
Driver IC
Output Voltage Regulation Target Vout: 24V
Light load switching mode selection FWPM - pin connected to VCC_DRIVER DEM - pin connected to GND
Type-2 Loop Compensation Network Frequency: 1.7kHz
Switching loop with current sensing circuitry
fs: 270kHz
Same policy as for input cap
